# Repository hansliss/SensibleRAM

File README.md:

# SensibleRAM

## NOTE: This doesn't currently work in a real VIC-20, since the address decoding for the VIA chips is incomplete, so they collide with this memory! I'm testing another patch to take care of that problem.

_A RAM expansion to make your VIC-20 more sensible_

This is actually how the VIC-20 should have been designed in the first place, hence the name SensibleRAM. It would have saved us all some headaches back in the day.

You may already know that there are many different cool modern memory expansion cartridges for the VIC-20 nowadays, providing up to 35-37kB of expansion memory. Some of that memory can benefit from this hack _if you are using BASIC_, whilst some of it is not relevant here. The aim here is to provide BASIC with as much memory as possible, regardless of what memory expansions you have.

_Before you spend a lot of time on this, please be aware that this is anachronistic nerdery of the highest degree. What this does would have been really cool in 1981. Forty years later, in 2021, not so much._

_Note that this hardware is as yet untested. The software has been tested in a patched VICE, however. Once I receive the boards and can test it properly, I'll update this and add some photos._

## Background

The VIC-20 has a somewhat confusing memory map. It comes with 5kB of system RAM as standard, with 1k at the bottom of the memory map, and 4k at $1000. To BASIC, those upper 4k are available as working memory, minus 0.5k that is used by the system for screen memory.

Normally, the screen memory is located at $1E00, so BASIC memory is $1000-$1DFF which is 3584 bytes. One byte is always consumed by BASIC, so the computer reports 3583 bytes free.

If you add a 3k RAM expansion, it will be located at $0400-0FFF, and the available space increases to 6655 bytes.

If you add larger expansions, they will start att BLK1 at $2000 and expand upwards until they reach $7FFF. However, when this happens, the screen memory becomes a problem, since at $1E00, it will split the system RAM in two non-contiguous parts. That won't do, so the screen memory is moved to $1000 if you add memory to BLK1, and all the memory between $1200 and $7FFF becomes usable to BASIC.

However, with one of those larger expansions in place, any 3k memory at $0400 becomes unusable to BASIC, since it ends up outside the contiguous area.

All this has two negative effects on the system:
1. The screen memory placement at either $1E00 or $1000 precludes any chance of getting contiguous memory between $0400 and $7FFF
1. the screen memory eats up 512 bytes that could have been used as BASIC memory.

## The hardware

The reason that the screen memory is located in one of those places as opposed to $0400 or $7E00 is the way the VIC chip is wired into the system. The screen memory has to be shared between the CPU and the VIC, and the VIC can only address 16k of memory.

The way this has been handled is that the VIC chip shares two different blocks with the CPU, BLK0 and BLK4. The VIC chip has 14 address bits. VA0-VA12 are connected via a tri-state buffer (controlled by a clock pin, but let's leave bus sharing out of this) to the CPU's CA0-CA12, but the most significant bit VA13 is connected to the active-low block selector /BLK4. This means that what the CPU sees as $0000-$1FFF, the VIC sees as $2000-$3FFF, and what the CPU sees as $8000-$9FFF is $0000-1FFF to the VIC.

There's also a mechanism explicitly blocking the VIC chip from sharing some areas with the CPU. Those include the three RAM blocks RAM[1-3] at $0400, the main expansion and ROM blocks BLK[1,2,3,5,6,7] (which have to be blocked since the VIC chip can't address them), and the two auxiliary I/O areas I/O2 and I/O3, located within BLK4. On top of that, the expansions we talked about earlier are all cartridge expansions, so they are sitting on the CPU bus rather than the VIC bus, which means they are unavailable to the VIC anyway.

## Conclusion

So, we're left with choosing an area within the interval $1000-$1FFF for the screen memory, since the first kB in BLK0 is used by the OS (although you can map the screen memory to the zero page, for a fun exercise), and BLK4, which is used only for the character ROM, the colour RAM and the I/O registers, doesn't have any available RAM.

Tough.

## The fix

_However_, the I/O registers at I/O0 ($9000-$93FF) take up far less than the entire interval, with the highest register at $912F. This leaves $9200-$93FF entirely free, and this area is addressable to both the CPU and the VIC.

So, this project adds 512 bytes of RAM to $9200, and with the included programs you can move the screen memory to this area on your VIC, freeing up 512 bytes of BASIC RAM. If you have both 3k and 8k+ expansions, you can also add those 3k to your available BASIC RAM, for a whopping total win of 3500 bytes.

The included assembly program will try to move the screen memory and start/end memory pointers as correctly as possible regardless of what memory expansions are present, and will then reinitialize BASIC.

Here's a short BASIC program that does the same, but assumes you have expansions in RAM[1-3] and BLK[1-3]:
```
10pO36866,pE(36866)or128:pO36869,(pE(36869)and15)or(4*16)
20pO648,146:pO44,4:pO43,1:pO56,128:pO55,0:pO642,4
30pO641,0:pO644,128:pO643,0:pO1024,0:sys58232
```

## The effects

Here are some examples of what happens when you use this with different expansions:

|Expansion|Orig. free ram|Orig max array size|New free RAM|New max array size|RAM increase|
|-----------|--------------|-------------------|------------|------------------|------------|
|None |3583 |1119 |4095 |1289 |512 |
|RAM[1-3] |6655 |2143 |7167 |2313 |512 |
|BLK1 |11775 |3848 |12287 |4021 |512
|RAM[1-3],<br>BLK1 |11775 |3848 | 15359 |5043 |3584 |
|BLK[1-2] |19967 |6581 |20479 |6751 |512 |
|RAM[1-3],<br>BLK[1-2] |19967 |6581 |23551 |7774 |3584 |
|BLK[1-3] |28159 |9310 |28671 |9480 |512 |
|RAM[1-3],<br>BLK[1-3] |28159 |9310 |31743 |10505 |3584 |

The "max array size" fields come from an experiment I did, using the BASIC program __testmem.bas__ that DIM'd string arrays of increasing size and filled them with strings, until no more memory was left. This program would have taken a week to run at the largest memory sizes, had I not run it in warp mode in VICE (see VICE_patching_notes.md).

## The future
Feel free to build on this! One possible addition would be to add an I/O location at, say $91FF, that causes the character ROM to be detached from the CPU bus and replaced with RAM, for an additional 4k of available RAM at $8000 - $8FFF, which is within the contiguous section. This would increase free space to 35839 bytes. Since this design uses a 32k chip which is 99.4% wasted, this would be a noble use of some of 
the space.

Please let me know what you come up with, and let me know if you actually try this thing out.

## Some technical notes without any explanatory text
```
bit 7 of $9002 controls A9 of screen memory and A9 of color memory
bit 4-7 of $9005 controls A10-A13 of VIC screen memory. A13 is /BLK4 to the CPU

$9200 = 1001 0010 0000 0000 = (VIC) b01001 000000000
$93FF = 1001 0011 1111 1111 = (VIC) b01001 111111111

!(A9 & A12 & !(A10 | A11 | A13))

A9:
$9002.7 = 1

A10-13:
$9005.4-7 = 0100
```

§1

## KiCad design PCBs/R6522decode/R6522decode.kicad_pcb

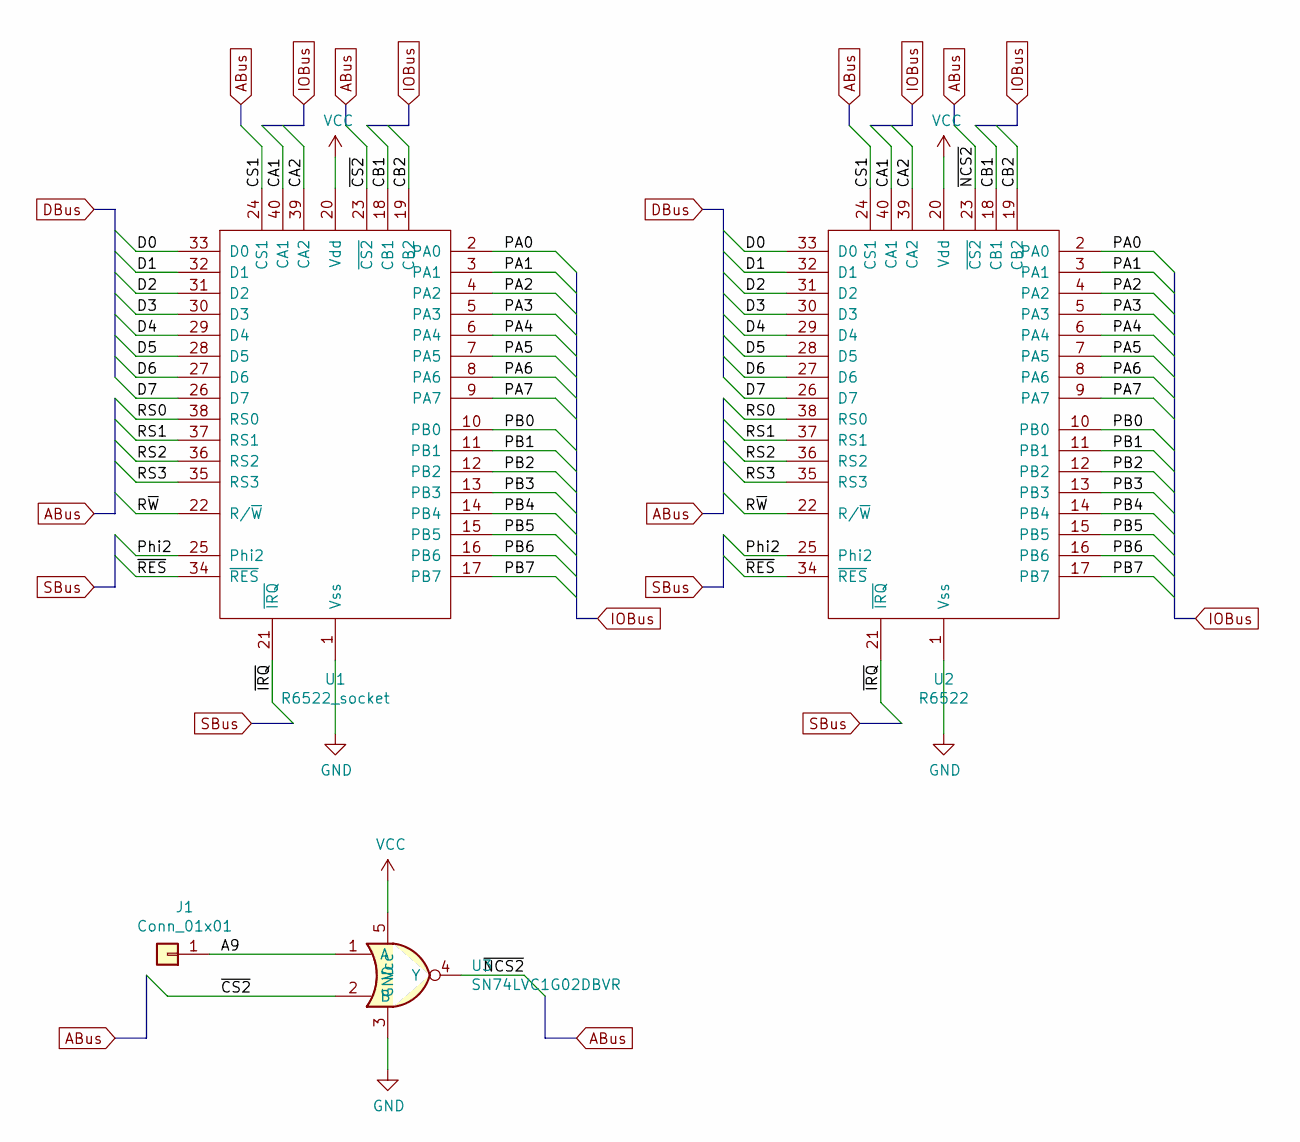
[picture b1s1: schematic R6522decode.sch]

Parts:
J1: Conn_01x01; Pin_Header_Straight_1x01_Pitch2.54mm
U1: R6522_socket; DIP-40_W15.24mm
U2: R6522; DIP-40_W15.24mm
U3: SN74LVC1G02DBVR; SOT-23-6_Handsoldering; LCSC C16360

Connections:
/A9: J1.1, U3.1 (A)
/CA1: U1.40 (CA1), U2.40 (CA1)
/CA2: U1.39 (CA2), U2.39 (CA2)
/CB1: U1.18 (CB1), U2.18 (CB1)
/CB2: U1.19 (CB2), U2.19 (CB2)
/CS1: U1.24 (CS1), U2.24 (CS1)
/D0: U1.33 (D0), U2.33 (D0)
/D1: U1.32 (D1), U2.32 (D1)
/D2: U1.31 (D2), U2.31 (D2)
/D3: U1.30 (D3), U2.30 (D3)
/D4: U1.29 (D4), U2.29 (D4)
/D5: U1.28 (D5), U2.28 (D5)
/D6: U1.27 (D6), U2.27 (D6)
/D7: U1.26 (D7), U2.26 (D7)
/PA0: U1.2 (PA0), U2.2 (PA0)
/PA1: U1.3 (PA1), U2.3 (PA1)
/PA2: U1.4 (PA2), U2.4 (PA2)
/PA3: U1.5 (PA3), U2.5 (PA3)
/PA4: U1.6 (PA4), U2.6 (PA4)
/PA5: U1.7 (PA5), U2.7 (PA5)
/PA6: U1.8 (PA6), U2.8 (PA6)
/PA7: U1.9 (PA7), U2.9 (PA7)
/PB0: U1.10 (PB0), U2.10 (PB0)
/PB1: U1.11 (PB1), U2.11 (PB1)
/PB2: U1.12 (PB2), U2.12 (PB2)
/PB3: U1.13 (PB3), U2.13 (PB3)
/PB4: U1.14 (PB4), U2.14 (PB4)
/PB5: U1.15 (PB5), U2.15 (PB5)
/PB6: U1.16 (PB6), U2.16 (PB6)
/PB7: U1.17 (PB7), U2.17 (PB7)
/Phi2: U1.25 (Phi2), U2.25 (Phi2)
/RS0: U1.38 (RS0), U2.38 (RS0)
/RS1: U1.37 (RS1), U2.37 (RS1)
/RS2: U1.36 (RS2), U2.36 (RS2)
/RS3: U1.35 (RS3), U2.35 (RS3)
/R~W: U1.22 (R/~W), U2.22 (R/~W)
/~CS2: U1.23 (~CS2), U3.2 (B)
/~IRQ: U1.21 (~IRQ), U2.21 (~IRQ)
/~NCS2: U2.23 (~CS2), U3.4 (Y)
/~RES: U1.34 (~RES), U2.34 (~RES)
GND: U1.1 (Vss), U2.1 (Vss), U3.3 (GND)
VCC: U1.20 (Vdd), U2.20 (Vdd), U3.5 (Vcc)

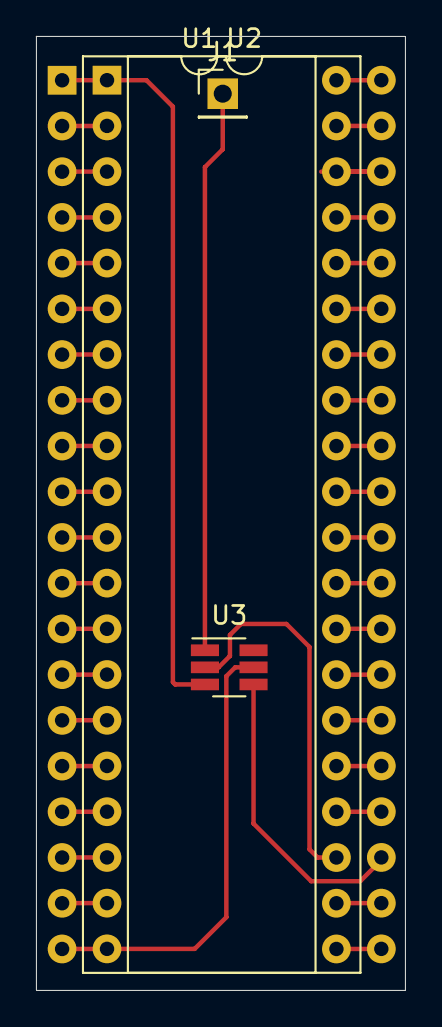
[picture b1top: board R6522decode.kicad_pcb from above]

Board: 2 copper layers, 20.5 x 53.0 mm, 4 parts (0 on the bottom side), 42 nets.

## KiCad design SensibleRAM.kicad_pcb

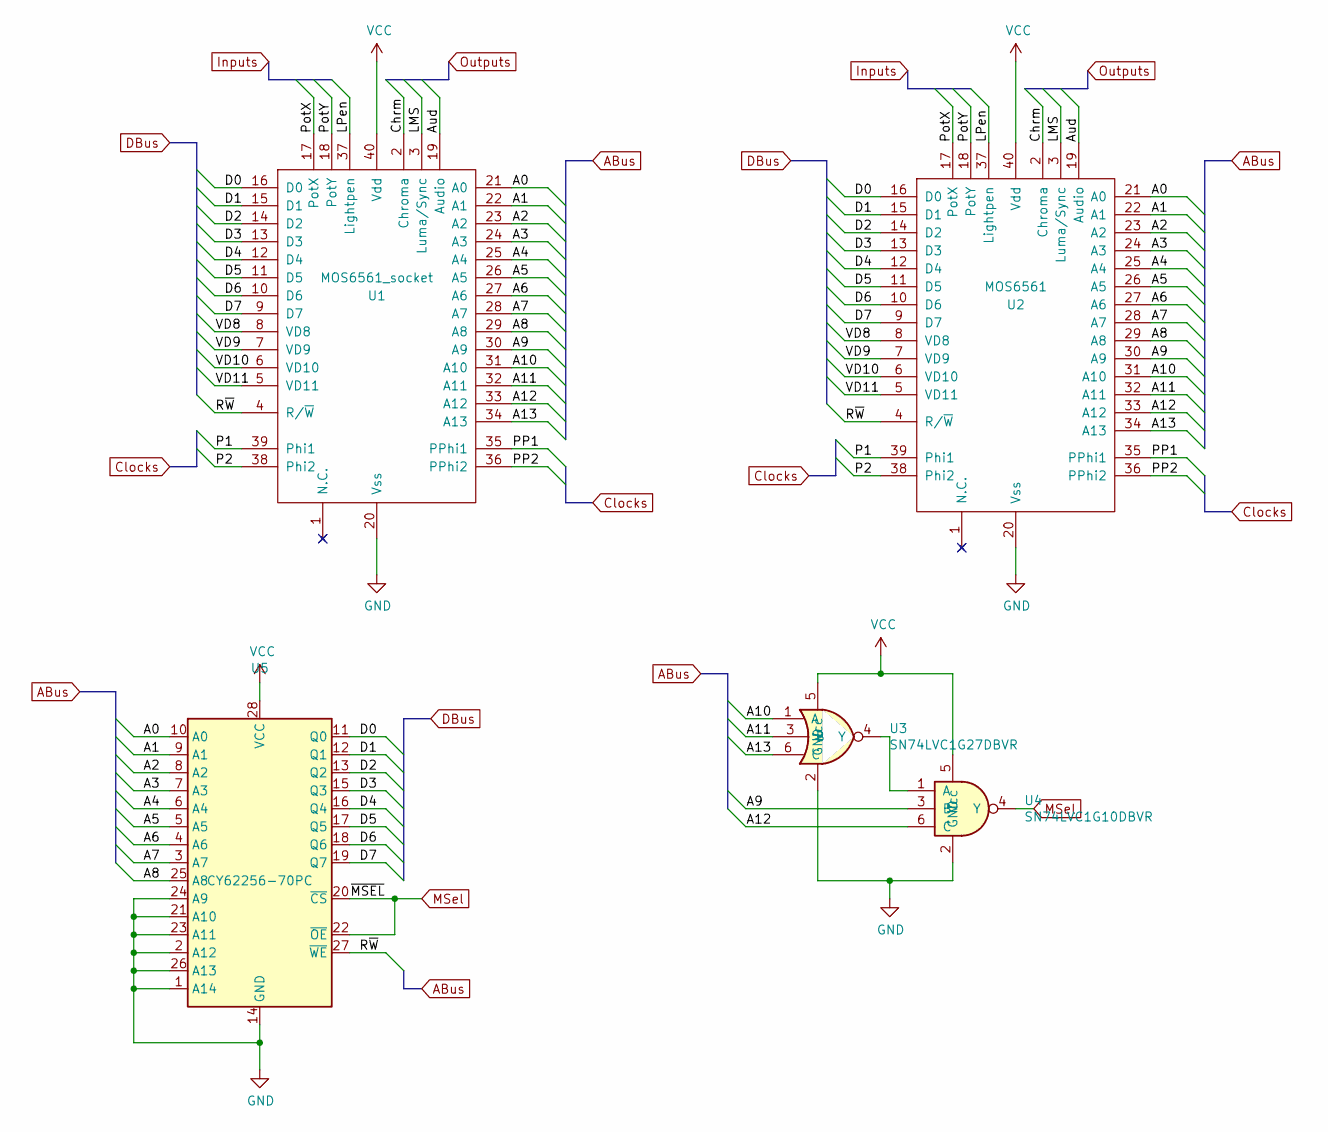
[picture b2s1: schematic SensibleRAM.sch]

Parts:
U1: MOS6561_socket; DIP-40_W15.24mm
U2: MOS6561; DIP-40_W15.24mm
U3: SN74LVC1G27DBVR; SOT-23-6_Handsoldering; LCSC C128410
U4: SN74LVC1G10DBVR; SOT-23-6_Handsoldering; LCSC C403721
U5: CY62256-70PC; SOP-28W_330mil_Pitch1.27mm; LCSC C261868

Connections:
/A0: U1.21 (A0), U2.21 (A0), U5.10 (A0)
/A1: U1.22 (A1), U2.22 (A1), U5.9 (A1)
/A2: U1.23 (A2), U2.23 (A2), U5.8 (A2)
/A3: U1.24 (A3), U2.24 (A3), U5.7 (A3)
/A4: U1.25 (A4), U2.25 (A4), U5.6 (A4)
/A5: U1.26 (A5), U2.26 (A5), U5.5 (A5)
/A6: U1.27 (A6), U2.27 (A6), U5.4 (A6)
/A7: U1.28 (A7), U2.28 (A7), U5.3 (A7)
/A8: U1.29 (A8), U2.29 (A8), U5.25 (A8)
/A9: U1.30 (A9), U2.30 (A9), U4.3 (B)
/A10: U1.31 (A10), U2.31 (A10), U3.1 (A)
/A11: U1.32 (A11), U2.32 (A11), U3.3 (B)
/A12: U1.33 (A12), U2.33 (A12), U4.6 (C)
/A13: U1.34 (A13), U2.34 (A13), U3.6 (C)
/Aud: U1.19 (Audio), U2.19 (Audio)
/Chrm: U1.2 (Chroma), U2.2 (Chroma)
/D0: U1.16 (D0), U2.16 (D0), U5.11 (Q0)
/D1: U1.15 (D1), U2.15 (D1), U5.12 (Q1)
/D2: U1.14 (D2), U2.14 (D2), U5.13 (Q2)
/D3: U1.13 (D3), U2.13 (D3), U5.15 (Q3)
/D4: U1.12 (D4), U2.12 (D4), U5.16 (Q4)
/D5: U1.11 (D5), U2.11 (D5), U5.17 (Q5)
/D6: U1.10 (D6), U2.10 (D6), U5.18 (Q6)
/D7: U1.9 (D7), U2.9 (D7), U5.19 (Q7)
/LMS: U1.3 (Luma/Sync), U2.3 (Luma/Sync)
/LPen: U1.37 (Lightpen), U2.37 (Lightpen)
/P1: U1.39 (Phi1), U2.39 (Phi1)
/P2: U1.38 (Phi2), U2.38 (Phi2)
/PP1: U1.35 (PPhi1), U2.35 (PPhi1)
/PP2: U1.36 (PPhi2), U2.36 (PPhi2)
/PotX: U1.17 (PotX), U2.17 (PotX)
/PotY: U1.18 (PotY), U2.18 (PotY)
/R~W: U1.4 (R/~W), U2.4 (R/~W), U5.27 (~WE)
/VD8: U1.8 (VD8), U2.8 (VD8)
/VD9: U1.7 (VD9), U2.7 (VD9)
/VD10: U1.6 (VD10), U2.6 (VD10)
/VD11: U1.5 (VD11), U2.5 (VD11)
GND: U1.20 (Vss), U2.20 (Vss), U3.2 (GND), U4.2 (GND), U5.1 (A14), U5.2 (A12), U5.14 (GND), U5.21 (A10), U5.23 (A11), U5.24 (A9), U5.26 (A13)
MSel: U4.4 (Y), U5.20 (~CS), U5.22 (~OE)
unnamed: U3.4 (Y), U4.1 (A)
VCC: U1.40 (Vdd), U2.40 (Vdd), U3.5 (Vcc), U4.5 (Vcc), U5.28 (VCC)

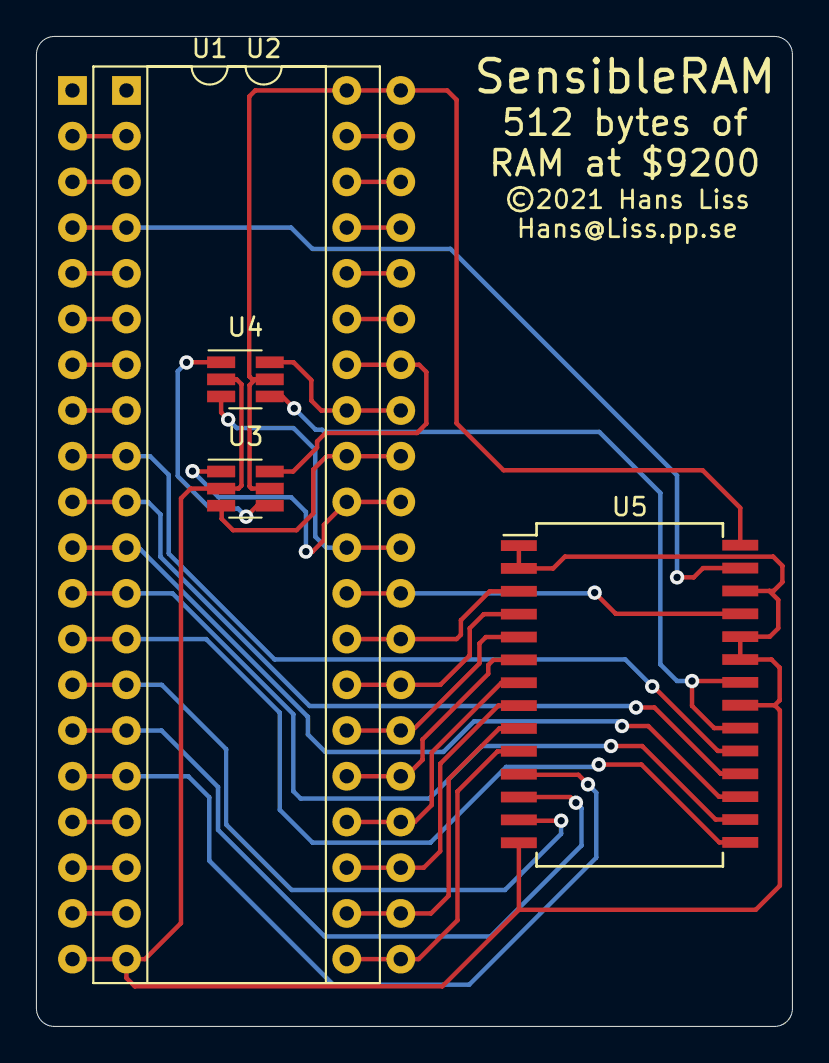
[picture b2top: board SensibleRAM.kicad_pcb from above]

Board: 2 copper layers, 42.0 x 55.0 mm, 5 parts (0 on the bottom side), 41 nets.

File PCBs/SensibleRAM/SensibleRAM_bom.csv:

Comment,Designator,Footprint,LCSC
"MOS6561_socket","U1","Housings_DIP:DIP-40_W15.24mm",""
"MOS6561","U2","Housings_DIP:DIP-40_W15.24mm",""
"SN74LVC1G27DBVR","U3","TO_SOT_Packages_SMD:SOT-23-6_Handsoldering","C128410"
"SN74LVC1G10DBVR","U4","TO_SOT_Packages_SMD:SOT-23-6_Handsoldering","C403721"
"CY62256-70PC","U5","VIC-20:SOP-28W_330mil_Pitch1.27mm","C261868"

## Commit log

2021-09-11 Initial import
2021-09-11 Removed SensibleRAM_notes.txt and moved the notes into README
2021-09-11 Fixed error in README
2021-09-11 Fixed README
2021-09-11 Cleaned up README
2021-09-11 Fixed header tag in README
2021-09-11 Fixed README Added patching notes for VICE
2021-09-20 Moved init code to $1200 Fixed missing connection on PCB Added note about incomplete decoding to README
2021-09-20 Missed connection on PCB
2021-09-22 Moved PCB designs down one level and added a new project for better address decoding for the VIAs.

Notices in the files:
SensibleRAM.kicad_pcb:
©2021 Hans Liss
